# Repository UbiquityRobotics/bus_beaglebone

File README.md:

# bus_beagle_bone

A Beagle Bone Black that can be connected to a bus.

The bus is a half-duplex multi-drop bus that runs at 500 Kbps.
It uses a Microchip MCP2562 CAN bus transceivers to connect to
the bus.

## Revision A

The schematic can be found in the `rev_a` folder as
`bus_raspberry_pi.pdf`.

### Power Supply

The power comes in on either N1 or N2.  These two connectors
are "daisy-chained" so that power can be routed to other boards.
The power goes through Q1 -- a P-channel MOSFET with a very low
R<Sub>ds</Sub>.  Q1 is used to prevent reverse polarity damage
just in case the power comes in reversed.  The power continues
to N6 which is a 5V DC-to-DC power converter that provides up
to 1.5 Amperes of output.  The 5V converter takes a nominal 24V
input with an absolute maximum of 36V.

### Bus Connection

The bus connection is on N3, which is a 2x5 .1 inch pitch
shrouded header.  LGND1 and LGND2 are connected to ground.
CANH and CANL are routed over to U2 which is the CAN bus
(more correctly -- a ISO-11898) transceiver -- a Microchip
MCP2562.  The TXD and RXD outputs are routed to the RXD1 and
TXD1 pins on the ATmega324P processor (U3).

### ISP Connection

The ISP connector is the 2x3 .1 inch pitch connector (N7)
that is connected to the MOSI, MISO, #RESET, and SCK pins
on the processor (U3).

### JTAG Connection

The JTAG connector is N9 which is also a .1 inch 2x5 shrouded
header.  The TDI, TDO, DMS, TCK, and #RESET lines are connected
to the appropriate JTAG pins on the processor (U3).

### 3.3 vs 5V Volt Issues

The processor (U3), AND gates (U1), and CAN bus transceiver (U2)
all run at 5V.  The USB to serial connectors (N4, N5) and the
Raspberry Pi connector (N10) use 3.3V signal levels.  Thus,
there are numerous places where 3.3V vs. 5V signal levels have
to be dealt with.

The signal level conversion is done with a 74HCT08 quad 2-input
AND gate (U1).  The HCT logic family is capable of converting TTL
voltage levels into "high" and "low" signals.  In particular,
the HCT logic family treats any voltage above 2.0V as a logic
"high."

There are 7 separate 22K/33K voltage dividers used for voltage
level issues.  The seven 22K resistors are contained in an 8-pin
SIP (Serial In-line Package.)  These seven resistors are named
R1A through R1F.  Likewise, the seven 33K resistors are contained
in another 8-pin SIP and are named R2A through R2F.  The voltage
dividers are deliberately arranged so that they have the letter
suffix -- R1A/R2A, ... , R1F/R2F.

The nominal center tap voltage of a 22K/33K voltage divider is:

    Vin * 33K/(22K+33K) = Vin * 3/5.

With Vin equal to 5 volts, the center tap voltage is 5V * 3/5 = 3V.

These 8-pin serial in-line packages have a resistance tolerance
of 2%.  This results in a center tap voltage range from 2.88V
to 3.12V.  2.88V is greater than the 2.0 Vih<Sub>min</Sub> for
the HCT logic family.  2.88V is also greater than .7*Vcc
(=.7*3.3V=2.31V) which is the standard Vin<Sub>min</Sub> for
standard CMOS.  3.12V is less than VCC (=3.3V).  Hence, the
voltage divider does not produce illegal 3.3V signaling levels.

Whenever a 5V output needs to be converted from 5 volts to 3V,
it directly fed into a voltage divider.  This occurs with R1D/R2D
connected to TXD0 of the processor (U4) and R1E/R2E and the
output of U1C.

The remaining five voltage dividers are all inputs of the 
74HCT08 quad AND gate package.  There are three cases to
be considered:

* When there is no connection, the voltage divider will 
  pull the input pin to a nominal 3V which is treated as
  a logic high.

* a 3.3V signal is connected, it will be at either 0V or 3.3V.
  In either case, the provided 3.3V voltage signal "overrides"
  the voltage divider.

* For the USB to serial connectors (N4, N5), it is possible
  to accidentally connect in a 5V USB to serial cable.  Again,
  in this case, the provided 5V voltage signal "overrides"
  the voltage divider.  The 74HCT05 is perfectly happy to
  tolerate a 5V input signal.

### Reset Circuitry

The reset signal can be sourced from four locations:

* The manual reset push button -- SW1,

* The #NRST on the JTAG connector (N9),

* The GPIO110_SPI1_SCLK pin on N10, and

* The #RTS signal (3.3V) on the programming FTDI connector (N4),

The push button is the simplest.  It connects the #RESET line
to ground when pushed.  Done.

Similarly, the #NRST line on the JTAG connector (N9) can be
driven low by a JTAG programmer/debugger.  Done.

Both the #RTS signal from N4 and the GPIO110_SPI1_SCLK pin
from N10 are used to trigger temporary reset pulse.  The basic
circuit is C6, D1 and R4 for #RTS/N4 and C8, D1 and R4.
Since the circuit is basically the same for both branches,
only the #RTS/N4 branch is explained.

The reset circuit from #RTS/N4 adheres to the Arduino defacto
standard for reset.  The signal comes in on pin 2 of U1A.
A voltage divider R1B/R2B holds the line at a nominal 3V
if no serial cable is plugged in.  Pin 1 of U1A is tied
to 5V so that U1A operates as a simple 3.3V to 5V voltage
level converter.

When the Arduino programmer (usually AVRDUDE) opens the connection
to the serial cable, #RTS (Request to Send) is driven low
for the duration of the programming session.  Capacitor C6, D1,
and R4 are used to convert the falling edge of #RTS into a
pulse onto the #RESET line.

* Prior to asserting #RTS low, the U1A 5V output and the
  R4 10K pull-up resistor hold both ends of capacitor C6
  at 5V.  This completely discharges C6.

* When #RTS goes low at the start of programming, the U1A
  output also goes low.  Since there is no voltage across
  C6, the other end of C6 is driven low as well.  This
  causes the #RESET line to be asserted low.

* Now C6 starts getting charged via R4 and starts to develop
  5V across C6.  Eventually the voltage across C6 will get
  high enough to de-assert #RESET and the processor (U3)
  will start to run the boot-loader.o

* When the programming session is over, #RTS is driven high.
  The causes the output of C6 to attempt to jump from 5V
  up to 10V.

<Pre>
        10V |                           *
            |                           **
            |                           * ***
            |                           *    ****
            |                           *        *****
        5V  ********              *******             *******
            |      *        ******      ^
            |      *    ****            |
            |      * ***                |
            |      **                   |
        0V  +------*--------------------|----------------------->
                                        |
                   ^                    |
                   |                    |
               #RTS goes low       #RTS goes high
</Pre>

* To prevent the voltage from going up to 10V, the Schottky
  diode D1 clamps the voltage to no more than 5.2V by very
  rapidly discharging C6.

The reason why a Schottky diode is used instead of a silicon
diode is because it unclear what the voltage tolerance of #NRST
of the JTAG programmer connector (N9) and the #RESET connector
of the ISP connector (N7) are.  By using a Schottky diode,
the voltage is clamped to 5.2V rather than 5.7.

### RXD and TXD Considerations

In general, the primary purpose of this board is to connect
TXD0 and RXD1 to GPIO2_UART2_RX and GPIO3_UART2_TX respectively.
In addition, it is desirable to allow the programming
connector (N5) to be used to program the processor (U4)
*and* to use the console connector (N5) to view the console
traffic from the Raspberry Pi on boot up.  To accomplish this
task some additional circuitry is used to OR the serial
cable TXD signals into the correct locations.

A key thing to understand about serial connections is that
the line idles "high".  U1B and U1D are AND gates.  Using
De Morgan's law, A.B = ~(~A + ~B).  Thus, using 2-input AND
gates, the signals a correctly OR'ed together so that when
both inputs are idling "high", the output is also "high".

There are three paths to follow:

* Processor (U4) <==> Raspberry Pi (N9),

* Processor (U4) <==> programmer connector (N2), and

* Processor (U4) <==> console connector (N3).

#### Processor to Raspberry Pi

In this situation, the 5V TXD0 output on the processor (U3)
is routed through the R1D/2D voltage divider to bring the
voltage down to a nominal 3.0V.  This signal is routed to U1C.
U1C converts the 3.0V signal to a 5V output which is again
divided back down to 3.0V via R1E/R2E.  This 3.0V signal goes
into GPIO2_UART2_RX on the Raspberry Pi.

In the reverse direction, the 3.3V output of GPIO15_TXD is
sent through the R1G/R2G voltage divider U1B which converts
it to a 5V output and directs it to RXD0 on the processor (U3).

#### Processor to Programmer Connector

In this situation, the 5V TXD0 output on the processor (U3)
is voltage divided by R1D/R2D down to 3.0V and goes to RXD
on the programmer connector (N2).

The 3.3V TXD output on the programmer connector (N2) is
routed to U1B which converts it up to 5V and routes the
signal into RXD0 input on the processor (U4).

#### Processor to Console Connector

In this situation, the 5V TXD0 output on processor (U4)
is voltage divided R1D/R2D down to 3.0V and to both U1C
and the RXD signal of N4.

The GPIO3_UART2_TX is routed through the R1G/R2G voltage
divider directly to the RXD pin of N5.

## LED Circuit

The LED circuit is provides a single LED (D2) that can be

* connected to the power supply to provide a power on LED, or

* connected to PB7/SCK (aka the Arduino D13 pin) of the
   processor (U3), or

* can be left unconnected.

This is accomplished using J1, R5, R6 and D2.

When pins 1 and 3 of J2 are shorted using a jumper, power is
routed from +5V through R6 through the LED (D2) to ground.

When pins 2 and 3 of J2 are shorted together, the output
of PB7/SCK of the processor (U3) is routed through R5 
through the LED to ground.

When pins 3 and 4 of J2 are shorted together, there is
no circuit path through LED (D2).

When pins 1 and 2 of J2 are accidentally shorted together,
resistors R5 and R6 form a voltage divider that simply
wastes power.  At least it does not accidentally short
the power supply to ground.

## Rev. A Issues

* JTAG NRST is not connected to #RESET. [x]

* R1D is connected to +5V not TXD0. [x]

* R1E is connected to +5V not U1C output. [x]

* R1G is connected to +5V not GPIO2_UART2_RX. [x]

* C6 and C8 should be 1uF. [x]

* The MCP2562 (U2) RxD and Txd (pins 1 and 4) are swapped. [x]

* Add 100K pull up resistor inputs that can be disconnected. [x]

* Make sure the BBB connector edge is clear of obsticles.
  Think about making N10 (the BBB connector) the full length. [x]

* Think about connecting MCP2562 (U2) STBY (pin 8) to a processor pin.

* Rotate N3 (the bus connector); it is pointing the wrong way. [x]

* C1 can be moved to be in line with C2. [x]

* N4 is labeled "CONSOLE" and N5 is labeled "PROGRAM".  This is backwards. [x]

* The artwork for N6 (the power supply connector) is backwards. [x]

## Rev. B Issues

* Move N10 closer to the PCB edge. [x]

* Think about add two pins next to N10 to prevent miss aligning
  N10 along the P9 row.  [Added N11, N12, and N13]

* Added real time clock. [x]

## Rev. C Issues

* Pin 10 of U1 has no 100K pull-up. [done]

* ISP connector is too close to real time clock to work with the
  Atmel-ICE programmer.  There is actually plenty of room around
  the crystal and load capacitors. [done]

* The hole for the plus terminal of the Litium battery is way
  too big.

* The 5mm Terminal blocks are oriented backwards. [removed]

* Think about changing the 1x1 mis-alignment pins for the
  BBB connector to 1x2's.  They would be easier to install. [done]

* Think about removing the R9/R10 pull-up resistors.  The BBB
  already has pull-up resistors. [done]

* The Lithium battery overlaps with the JTAG connector.  Perhaps
  rearrange. [done]

* There is no filter capacitor for the real time clock.

* The RC constant of R4 * (C6 + C8) needs to be small enough
  that the circuit will actually reset before jumping to location 0.
  When both C6 and C8 are 1uF, the RC constant is too big.
  Thus, probably C6 and C8 should be set to .1uF. [done]

* N7 is too close to N6.  It is really hard to jumper the LED
  to be connected to D13. [5V Regulator changed]

* N6 is artwork is not next to actual N6 connector. [done]

* N6 would have mechanical interferance with N2. [done]

* Think about adding lines to the BBB POWER button and reset.
  [not done]

* The Ground on pins 1 and 2 of the BBB connector is not very good.
  [done]

* Pin 31 is hooked to a high frequency SPI signal.  It should be
  connected to a slower GPIO line. [done]

* Think about adding a female USB A connector to provide 5V to
  other devices that need 5V. [see bus_usb_power]

## ROS Integration

It is desirable to have excellent ROS integration with "the bus".
The bus has the following features:

* Discovery.  The head processor can scan the bus and find all
  modules that are plugged into it.  Currently, hot plugging
  is not allowed, but it could if future versions.

* Flexibility.  While bus modules can be dedicated to a single
  task, some of them are more fleximble.  For example,

  * bus_grove12 can be connected to 100+ different Grove system modules.

  * bus_micro?? can be connected to 100+ diffeent MikroBus modules.

  * bus_dynabus can be connected to dozens of Dynamixel servos.

* Field Upgradable. The firmware for each module can be upgraded
  of the bus.

The bus is basically operated in a master/slave mode.  ROS talks
to a bus master (e.g. bus_beaglebone) via a serial protocol.
The bus master talks to the bus modules using bus protocol.

The ROS bus node is a ROS node that talks to the bus master
over a serial line.  Only the ROS bus node is allowed to use
the serial line connected to the bus master.  Any other ROS
nodes that need to access the bus must do so through the ROS
Bus node.

It is anticipated that each bus module will have a corresponding
ROS node that is responsible for the bus module.  

correspondance to bus modules and a ROS node to control the
bus module.  For example, the bus_sonar10 module will have
a didicated ROS Sonar10 node.  

### ROS Bus Node

The basic concept behind the ROS Bus Node is that allows other
ROS nodes to talk to the bus via a modes number of ROS service
(i.e. Remote Procedure Call) requests.

        login("node id TBD") => session
            Returns a session handle for subsequent requests.

        logout(session)
            Lets Bus Node that session is not to be accepted
            anymore.

        bus_search(session, vendor_id, product_id) => [bus_uid,...]
            Return list of bus_uid's for bus modules that match
            vendor_id and product_id.  vendor_id and product_id
            can be set to 0 to matach all.

        hardware_version(session, bus_uid) => hardware_version
            Return the hardware version for bus_uid.

        firmware_version(session, bus_uid) => (major, minor)
            Return the major and minor software version numbers
            for bus_uid.

        attach(session, bus_uid, share) => module
            Returns a module handle for talking to the bus_id.
            Set share to 1 for a sharable module and to 0 for
            exclusive use.

        release(session, module)
            Releases module.

        transfer(session, module, priority, [byte, ...]) => [byte, ...]
            This is the generic bus message send receive message.
            Mostly, people will use higher level commands.  Priority
            specifies the immediacy of the message.

        register_get(session, module, priority, register) => value
            Set register to value.  Value is is a scalar value
            that is up to 32-bits.

        register_set(session, module, priority, register, value, size)
            Set register to value.  Value is is a scalar value
            that is up to 32-bits in size.  size specifies the number
            bytes.

        string_get(session, module, priority, register) => "text"
            Get a string value from a string register.

## Bus_Bridge_Encoders_Sonar Node

Basically this node has to emulate the functionality of the
ROS Arduino Bridge.

* Publish odometry data

* Accept drive requests (i.e. speed and twist)

* Publish sonar data

## Serial Line Protocol

        Host => Coprocessor:

            1100 00hh        Set hh
            1100 0100        Do Discovery scan
            1100 0101        Reset bus
            1100 0110        Reserved
            1100 0111        Reserved

            xyyy yyyy        if (hh > 0) { send (h hyyy yyyy); hh = -1; }
                                     else      { send (0 xyyy yyyy); }

        Coprocessor => Host:
            a xxxx xxxx	     Send xxxx xxxx to host (9th bit is lost)

## Installing ROS Hydro Onto a Micro-SD Card

1. Create a ros-bbb directory:

        cd ...
        mkdir ros-bbb
        cd ros-bbb

2. Download the following three files from ros-training.com:

        wget http://www.ros-training.com/static/media/ros-bbb/ubuntu_ros_partitions.sfdisk
        wget http://www.ros-training.com/static/media/ros-bbb/ubuntu_ros_boot.partimg.gz.000
        wget http://www.ros-training.com/static/media/ros-bbb/ubuntu_ros_rootfs.partimg.gz.000

3. Verify that you got files that are the right size:

        ls -la
        -rw-rw-r-- 1 wayne wayne   6916451 Aug 22 08:01 ubuntu_ros_boot.partimg.gz.000
        -rw-rw-r-- 1 wayne wayne       259 Aug 22 08:01 ubuntu_ros_partitions.sfdisk
        -rw-rw-r-- 1 wayne wayne 345502689 Aug 22 08:09 ubuntu_ros_rootfs.partimg.gz.000

4. *Before* put your micro-SD card in, see what /dev/sd* says:

        ls -l /dev/sd*
        brw-rw---- 1 root disk 8,  0 Aug 22 10:33 /dev/sda
        brw-rw---- 1 root disk 8,  1 Aug 22 10:33 /dev/sda1
        brw-rw---- 1 root disk 8,  2 Aug 22 10:33 /dev/sda2
        brw-rw---- 1 root disk 8,  3 Aug 22 10:33 /dev/sda3
        brw-rw---- 1 root disk 8,  4 Aug 22 10:33 /dev/sda4
        brw-rw---- 1 root disk 8,  5 Aug 22 10:33 /dev/sda5
        brw-rw---- 1 root disk 8,  6 Aug 22 10:33 /dev/sda6
        brw-rw---- 1 root disk 8,  7 Aug 22 10:33 /dev/sda7

5. Now insert your 8GB (or larger) micro-SD card into the slot and
   do another ls command:

        ls -l /dev/sd*
        brw-rw---- 1 root disk 8,  0 Aug 22 10:33 /dev/sda
        brw-rw---- 1 root disk 8,  1 Aug 22 10:33 /dev/sda1
        brw-rw---- 1 root disk 8,  2 Aug 22 10:33 /dev/sda2
        brw-rw---- 1 root disk 8,  3 Aug 22 10:33 /dev/sda3
        brw-rw---- 1 root disk 8,  4 Aug 22 10:33 /dev/sda4
        brw-rw---- 1 root disk 8,  5 Aug 22 10:33 /dev/sda5
        brw-rw---- 1 root disk 8,  6 Aug 22 10:33 /dev/sda6
        brw-rw---- 1 root disk 8,  7 Aug 22 10:33 /dev/sda7
        brw-rw---- 1 root disk 8, 16 Aug 22 18:50 /dev/sdb
        brw-rw---- 1 root disk 8, 17 Aug 22 18:50 /dev/sdb1

   Notice that /dev/sdb and /dev/sdb1 showed up.  If something
   else shows up, you are going to need to manually edit
   ubuntu_ros_partitions.sfdisk file.  In addition, everywhere in
   the instructions below, you are going to have to change
   "/dev/sdb..." into /dev/sdX..." where "X" is the correct
   micro-SD drive letter.  If this does not make any sense,
   *get some help*.

6. I do the next commands as root:

        sudo bash
        Password: {your root password here}

7. Make sure that the partimage command is installed:

        apt-get install partimage
        {Respond positively to all prompts}

8. Make darn sure that /dev/sdb* is not installed:

        umount /dev/sdb*
        {It should say everything is unmounted}

9. Install a partition table on /dev/sdb:

        sfdisk --force /dev/sdb < ubuntu_ros_partitions.sfdisk
        partprobe /dev/sdb
        partprobe -s /dev/sdb

   The partprobe -s command may mention "msdos", just ignore that.

10. Now install boot image on micro-SD card:

        partimage restore /dev/sdb1 ubuntu_ros_boot.partimg.gz.000

    This will bring up one of the fake ASCII window system.
    You can use [Tab] to advance from one option to the next
    You can use [space] to toggle an option.
    You can type [enter] to trigger everything.
    For this screen I only toggle the option that writes 0's
    to empty blocks.  It is probably unnecessary, but I like
    to be sure.  Type [enter] at the continue option.  Keep
    typing [Tab]'s and [returns] until it actually write the
    partition bits.  The program will finish and then pause
    for a while as it finishes flushing the bits out to the
    micro-SD card.  Just be patient.

11. Now install rootfs partition onto the micro-SD card:

        partimage restore /dev/sdb2 ubuntu_ros_rootfs.partimg.gz.000
                
    Go through the same steps as in step 10.

12. Make darn sure that /dev/sdb* is unmounted:

        umount /dev/sdb*
        {It should say everything is no longer mounted}

14. Make sure that minicom is installed:

        apt-get install minicom

14. Exit from root:

        exit

15. Yank the micro-SD card out of your machine.

16. Grab your Beaglebone Black (henecforth called BBB.)  Flip it
    over and install the micro-SD card.

17. Find two open USB ports on your laptop/desktop.  Plug your
    FTDI 3.3V USB to serial cable into one of the USB ports.
    Make *darn* sure that you have a 3.3V FTDI cable.  If you
    are using one of Wayne's FTDI cables with tape wrapped
    arround the pin, peel the tape back and make *sure* it
    says "3V3" on the USB connector.  Plug the short USB to
    mini-USB cable that came with your BBB into the other USB
    port on laptop/desktop.  Do *not* plug the other end of
    this cable into the BBB yet.

18. On the top of the BBB, there is a 1x6 pin header labeled J1.
    One of the pins has a white dot next to the pin.  Plug in
    the 1x6 female receptical on the FTDI cable such that the
    black wire goes into the next the white dot.

19. Fire up the minicom terminal emulator:

        minicom

    Make sure the baud rate is "115200 8N1".  It should specify
    that it is using a serail cable like /dev/ttyUSB0.

20. Locate the little black button on the top surface of the BBB
    on that is near the micro-SD card (which is on the back surface).
    This button is very close to one of the mounting holes.  Also
    locate the micro-USB connector on the back side of the BBB
    near the Ethernet Jack (which is on the front side.)

21. Now we will carefully power up the BBB.  This is done by:

    A. Press down the black button and *hold* it down.
    B. While leaving the black button held down, plug in
       the power micro-SD.
    C. The blue LED's flash on the BBB.
    D. Boot up text spews out on the minicom window.

22. In fairly short order, Linux 13.04 will boot up and prompt
    you to login.  You can login as either user "ubuntu" with
    password "temppwd" or as user "ros" with password "training".

23. After you have logged in, you can poke around.  Verity that
    the directory "/opt/ros/hydro" exists.

24. Now you can shut down the BBB:

        sudo halt
        Password: {Use "temppwd" or "training")

    Some lights flash and some text spews.  Eventually the BBB
    stops.

25. Remove power cable and USB-to Serial cable.

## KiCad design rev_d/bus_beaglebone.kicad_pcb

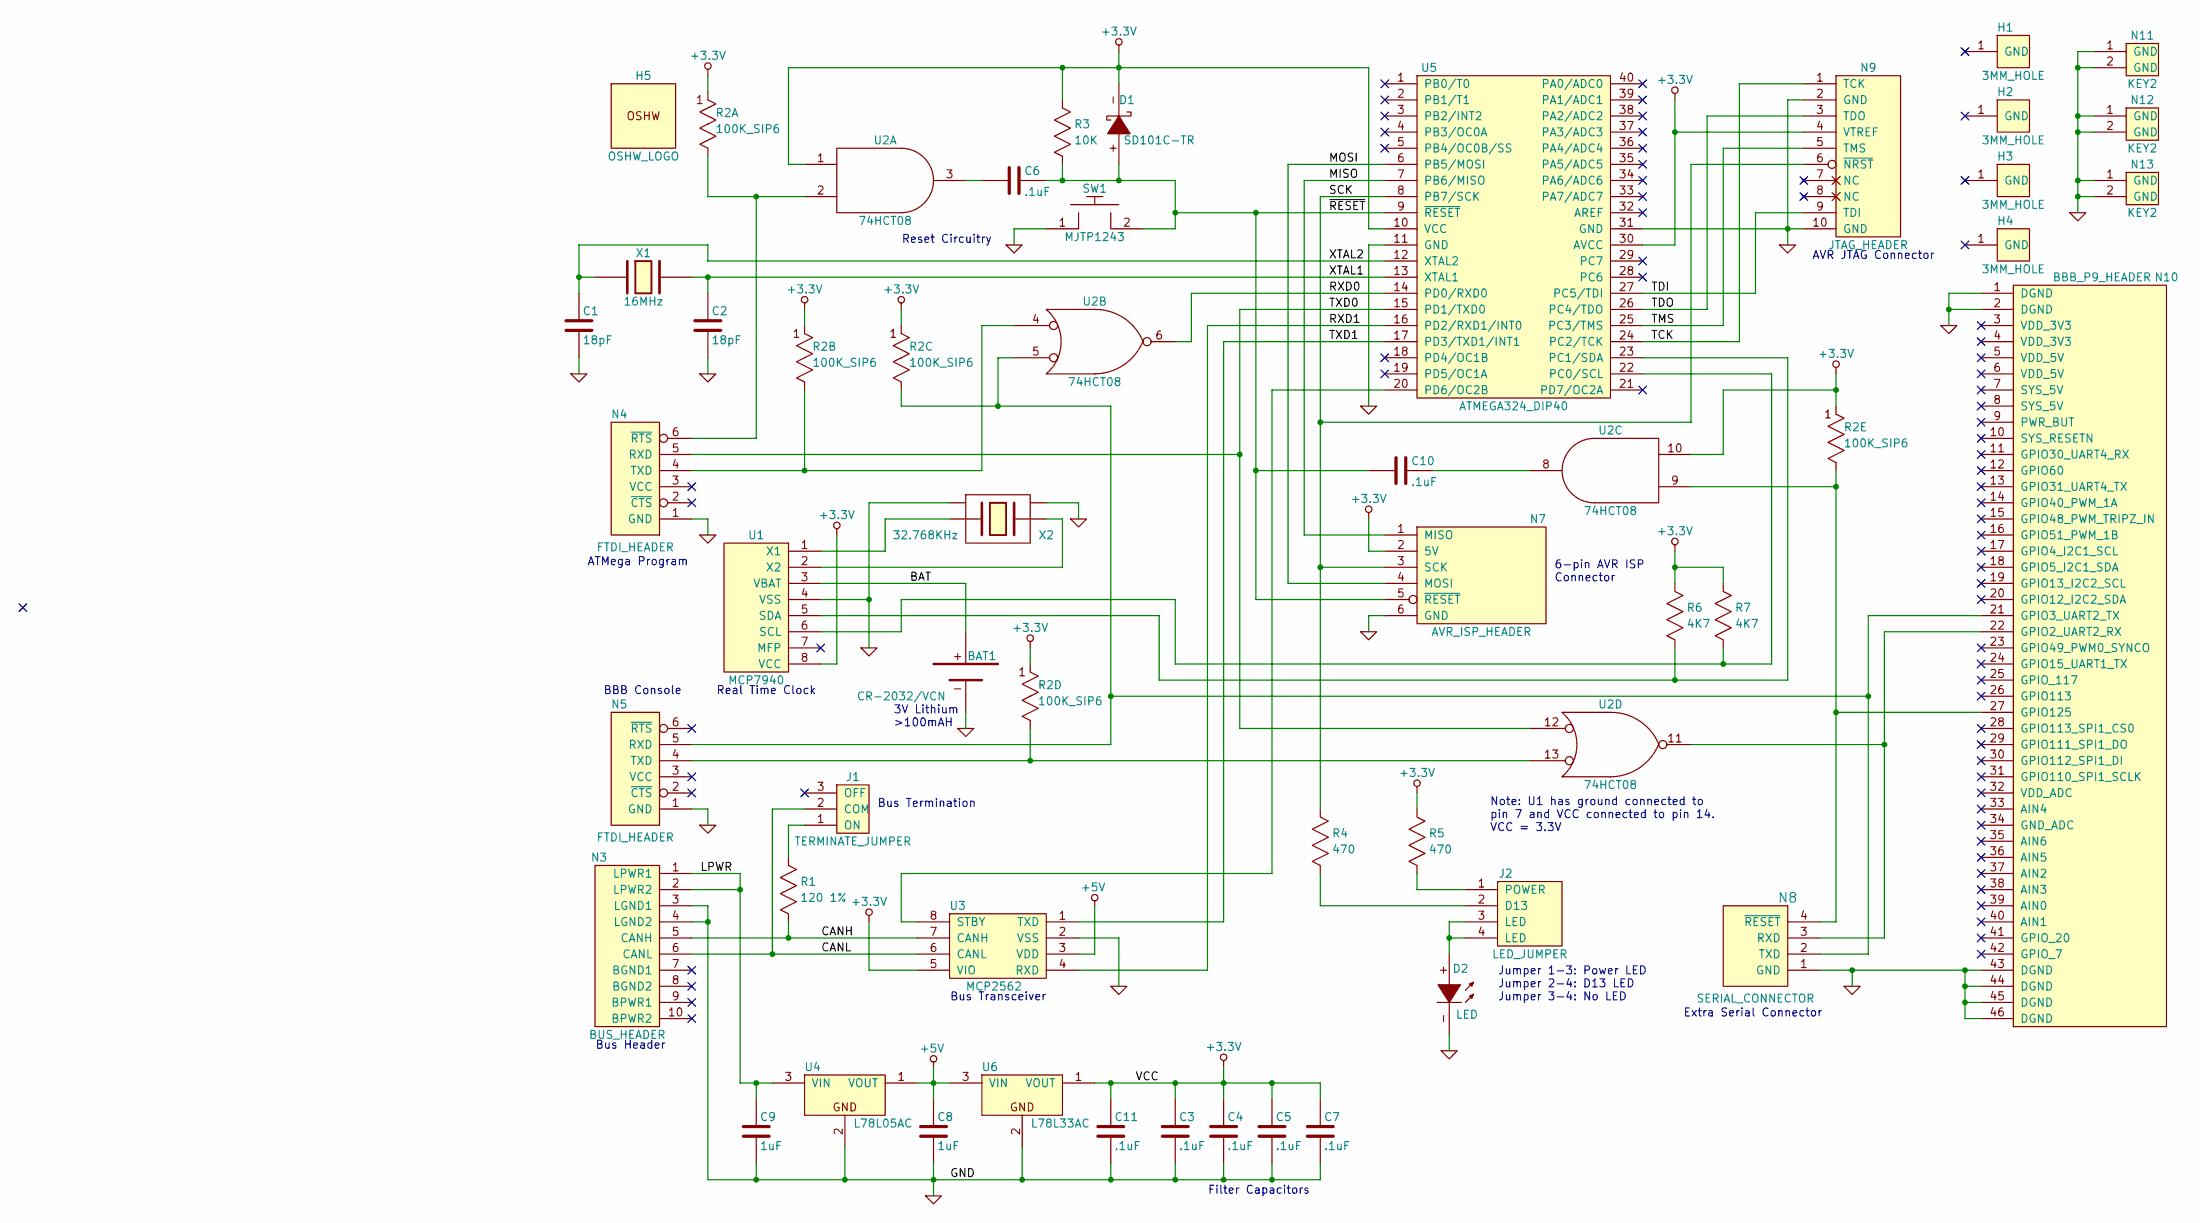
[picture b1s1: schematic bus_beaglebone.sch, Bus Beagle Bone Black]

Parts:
BAT1: CR-2032/VCN; 10MM_BATTERY
C1, C2: 18pF; Capacitor3MMDiscRM2.5
C3, C4, C5, C6, C7, C10, C11: .1uF; Capacitor3MMDiscRM2.5
C8, C9: 1uF; Capacitor3MMDiscRM2.5
D1: SD101C-TR; Diode_DO-41_SOD81_Horizontal_RM10
D2: LED; T1_LED
H1, H2, H3, H4: 3MM_HOLE; MountingHole_3mm
H5: OSHW_LOGO; OSHW_LOGO_250mil
J1: TERMINATE_JUMPER; Pin_Header_Straight_1x03
J2: LED_JUMPER; Pin_Header_Straight_2x02
N3: BUS_HEADER; Pin_Header_Straight_2x05_Shrouded
N4, N5: FTDI_HEADER; Pin_Header_Straight_1x06
N7: AVR_ISP_HEADER; Pin_Header_Straight_2x03
N8: SERIAL_CONNECTOR; Pin_Header_Straight_1x04
N9: JTAG_HEADER; Pin_Header_Straight_2x05_Shrouded
N10: BBB_P9_HEADER; Pin_Header_Straight_2x23
N11, N12, N13: KEY2; Pin_Header_Straight_1x02
R1: 120 1%; Resistor_Horizontal__400
R2: 100K_SIP6; Pin_Header_Straight_1x06
R3: 10K; Resistor_Horizontal__400
R4, R5: 470; Resistor_Horizontal__400
R6, R7: 4K7; Resistor_Horizontal__400
SW1: MJTP1243; Button_6.5MM
U1: MCP7940; DIP-8__300
U2: 74HCT08; DIP-14__300
U3: MCP2562; DIP-8__300
U4: L78L05AC; TO92_123
U5: ATMEGA324_DIP40; DIP-40__600
U6: L78L33AC; TO92_123
X1: 16MHz; Crystal_HC49-U_Vertical
X2: 32.768KHz; RTC_CRYSTAL

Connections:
+3.3V: C3.1, C4.1, C5.1, C7.1, C11.1, D1.-, N7.2 (5V), N9.4 (VTREF), R2.1, R3.2, R5.2, R6.2, R7.2, U1.8 (VCC), U2.1, U2.10, U2.14 (VCC), U3.5 (VIO), U5.10 (VCC), U5.30 (AVCC), U6.1 (VOUT)
+5V: C8.1, U3.3 (VDD), U4.1 (VOUT), U6.3 (VIN)
/BAT: BAT1.+, U1.3 (VBAT)
/CANH: N3.5 (CANH), R1.1, U3.7 (CANH)
/CANL: J1.2 (COM), N3.6 (CANL), U3.6 (CANL)
/LPWR: C9.1, N3.1 (LPWR1), N3.2 (LPWR2), U4.3 (VIN)
/MISO: N7.1 (MISO), U5.7 (PB6/MISO)
/MOSI: N7.4 (MOSI), U5.6 (PB5/MOSI)
/RXD0: U2.6, U5.14 (PD0/RXD0)
/RXD1: U3.4 (RXD), U5.16 (PD2/RXD1/INT0)
/SCK: N7.3 (SCK), N9.6 (~NRST), R4.2, U5.8 (PB7/SCK)
/TCK: N9.1 (TCK), U5.24 (PC2/TCK)
/TDI: N9.9 (TDI), U5.27 (PC5/TDI)
/TDO: N9.3 (TDO), U5.26 (PC4/TDO)
/TMS: N9.5 (TMS), U5.25 (PC3/TMS)
/TXD0: N4.5 (RXD), U2.12, U5.15 (PD1/TXD0)
/TXD1: U3.1 (TXD), U5.17 (PD3/TXD1/INT1)
/XTAL1: C2.1, U5.13 (XTAL1), X1.2
/XTAL2: C1.1, U5.12 (XTAL2), X1.1
/~RESET: C6.2, C10.1, D1.+, N7.5 (~RESET), R3.1, SW1.2, U5.9 (~RESET)
GND: BAT1.-, C1.2, C2.2, C3.2, C4.2, C5.2, C7.2, C8.2, C9.2, C11.2, D2.-, N3.3 (LGND1), N3.4 (LGND2), N4.1 (GND), N5.1 (GND), N7.6 (GND), N8.1 (GND), N9.2 (GND), N9.10 (GND), N10.1 (DGND), N10.2 (DGND), N10.43 (DGND), N10.44 (DGND), N10.45 (DGND), N10.46 (DGND), N11.1, N11.2, N12.1, N12.2, N13.1, N13.2, SW1.1, U1.4 (VSS), U2.7 (GND), U3.2 (VSS), U4.2, U5.11 (GND), U5.31 (GND), U6.2, X2.3 (GND), X2.4 (GND)
unnamed: C6.1, U2.3
unnamed: C10.2, U2.8
unnamed: D2.+, J2.3 (LED), J2.4 (LED)
unnamed: J1.1 (ON), R1.2
unnamed: J2.1 (POWER), R5.1
unnamed: J2.2 (D13), R4.1
unnamed: N4.4 (TXD), R2.3, U2.4
unnamed: N4.6 (~RTS), R2.2, U2.2
unnamed: N5.4 (TXD), R2.5, U2.13
unnamed: N5.5 (RXD), N8.2 (TXD), N10.21 (GPIO3_UART2_TX), R2.4, U2.5
unnamed: N8.3 (RXD), N10.22 (GPIO2_UART2_RX), U2.11
unnamed: N8.4 (~RESET), N10.27 (GPIO125), R2.6, U2.9
unnamed: R6.1, U1.5 (SDA), U5.23 (PC1/SDA)
unnamed: R7.1, U1.6 (SCL), U5.22 (PC0/SCL)
unnamed: U1.1 (X1), X2.1
unnamed: U1.2 (X2), X2.2
unnamed: U3.8 (STBY), U5.20 (PD6/OC2B)

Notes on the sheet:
BBB Console
ATMega Program
Note: U1 has ground connected to pin 7 and VCC connected to pin 14. VCC = 3.3V
Bus Header
6-pin AVR ISP Connector
Jumper 1-3: Power LED Jumper 2-4: D13 LED Jumper 3-4: No LED
Filter Capacitors
Bus Transceiver
Reset Circuitry
AVR JTAG Connector
3V Lithium >100mAH
Real Time Clock
Bus Termination
Extra Serial Connector

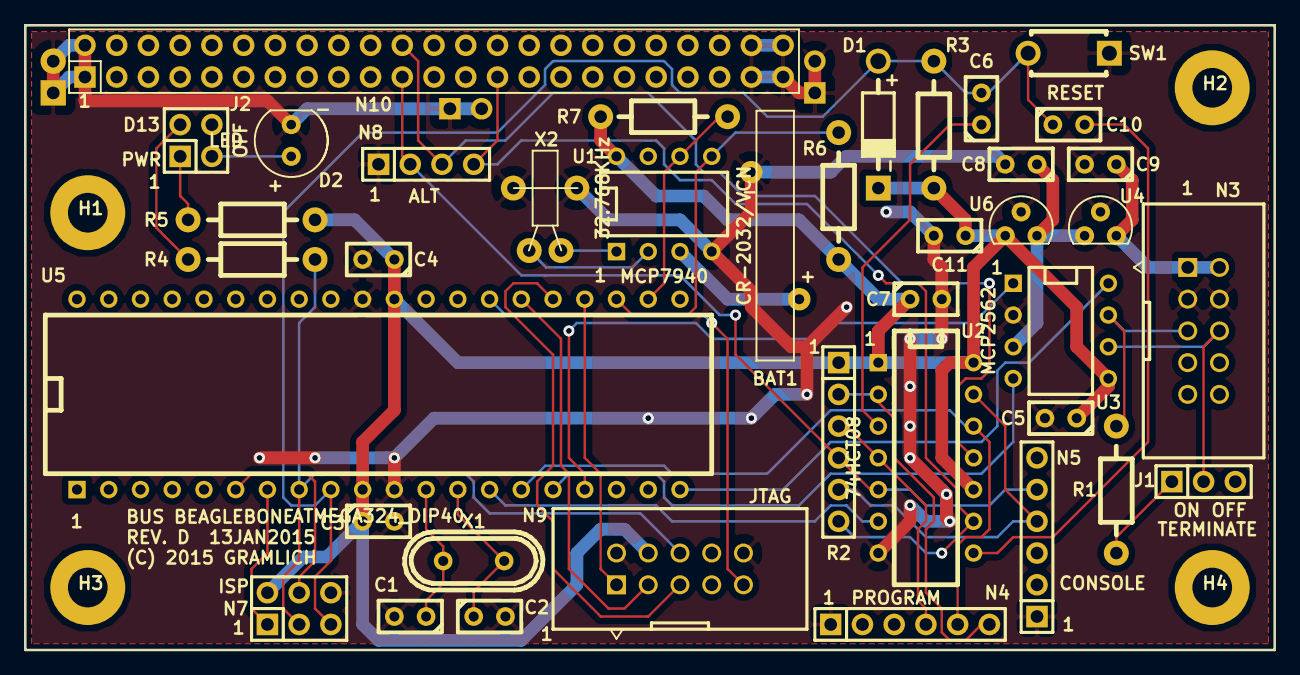
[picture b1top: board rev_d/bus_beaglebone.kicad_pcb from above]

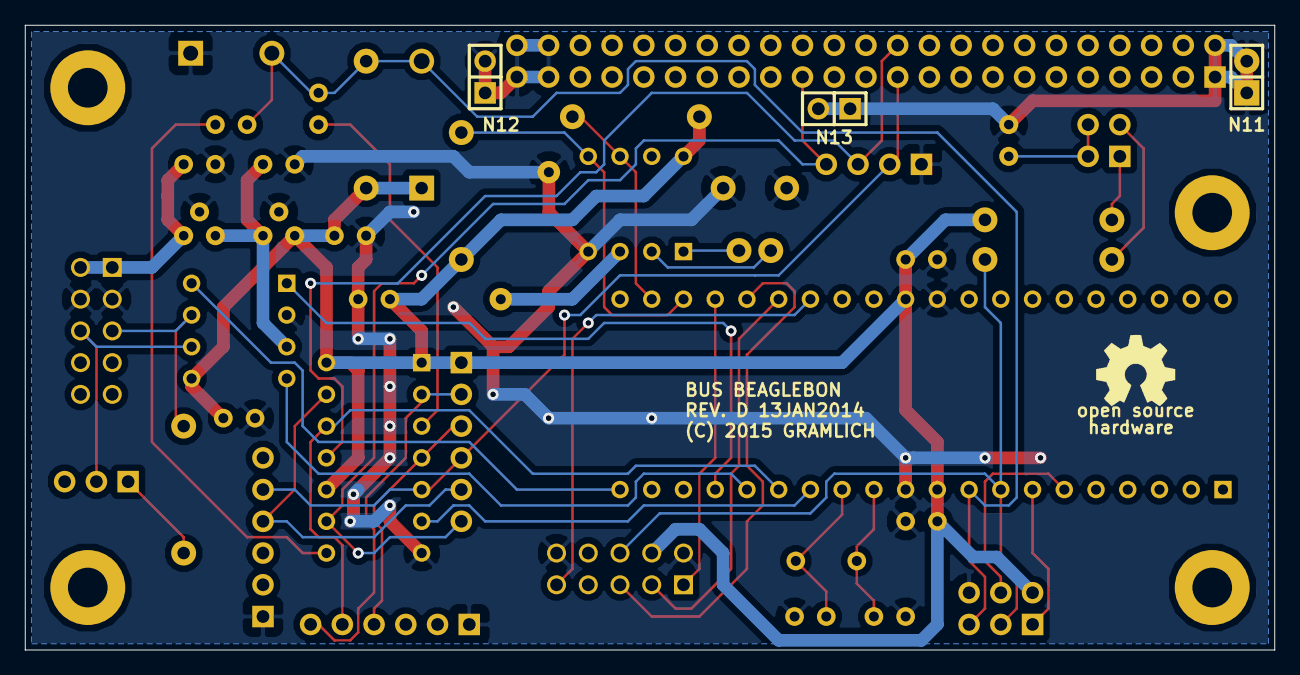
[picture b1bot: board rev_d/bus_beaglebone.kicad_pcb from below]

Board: 2 copper layers, 100.0 x 50.0 mm, 47 parts (4 on the bottom side), 38 nets.

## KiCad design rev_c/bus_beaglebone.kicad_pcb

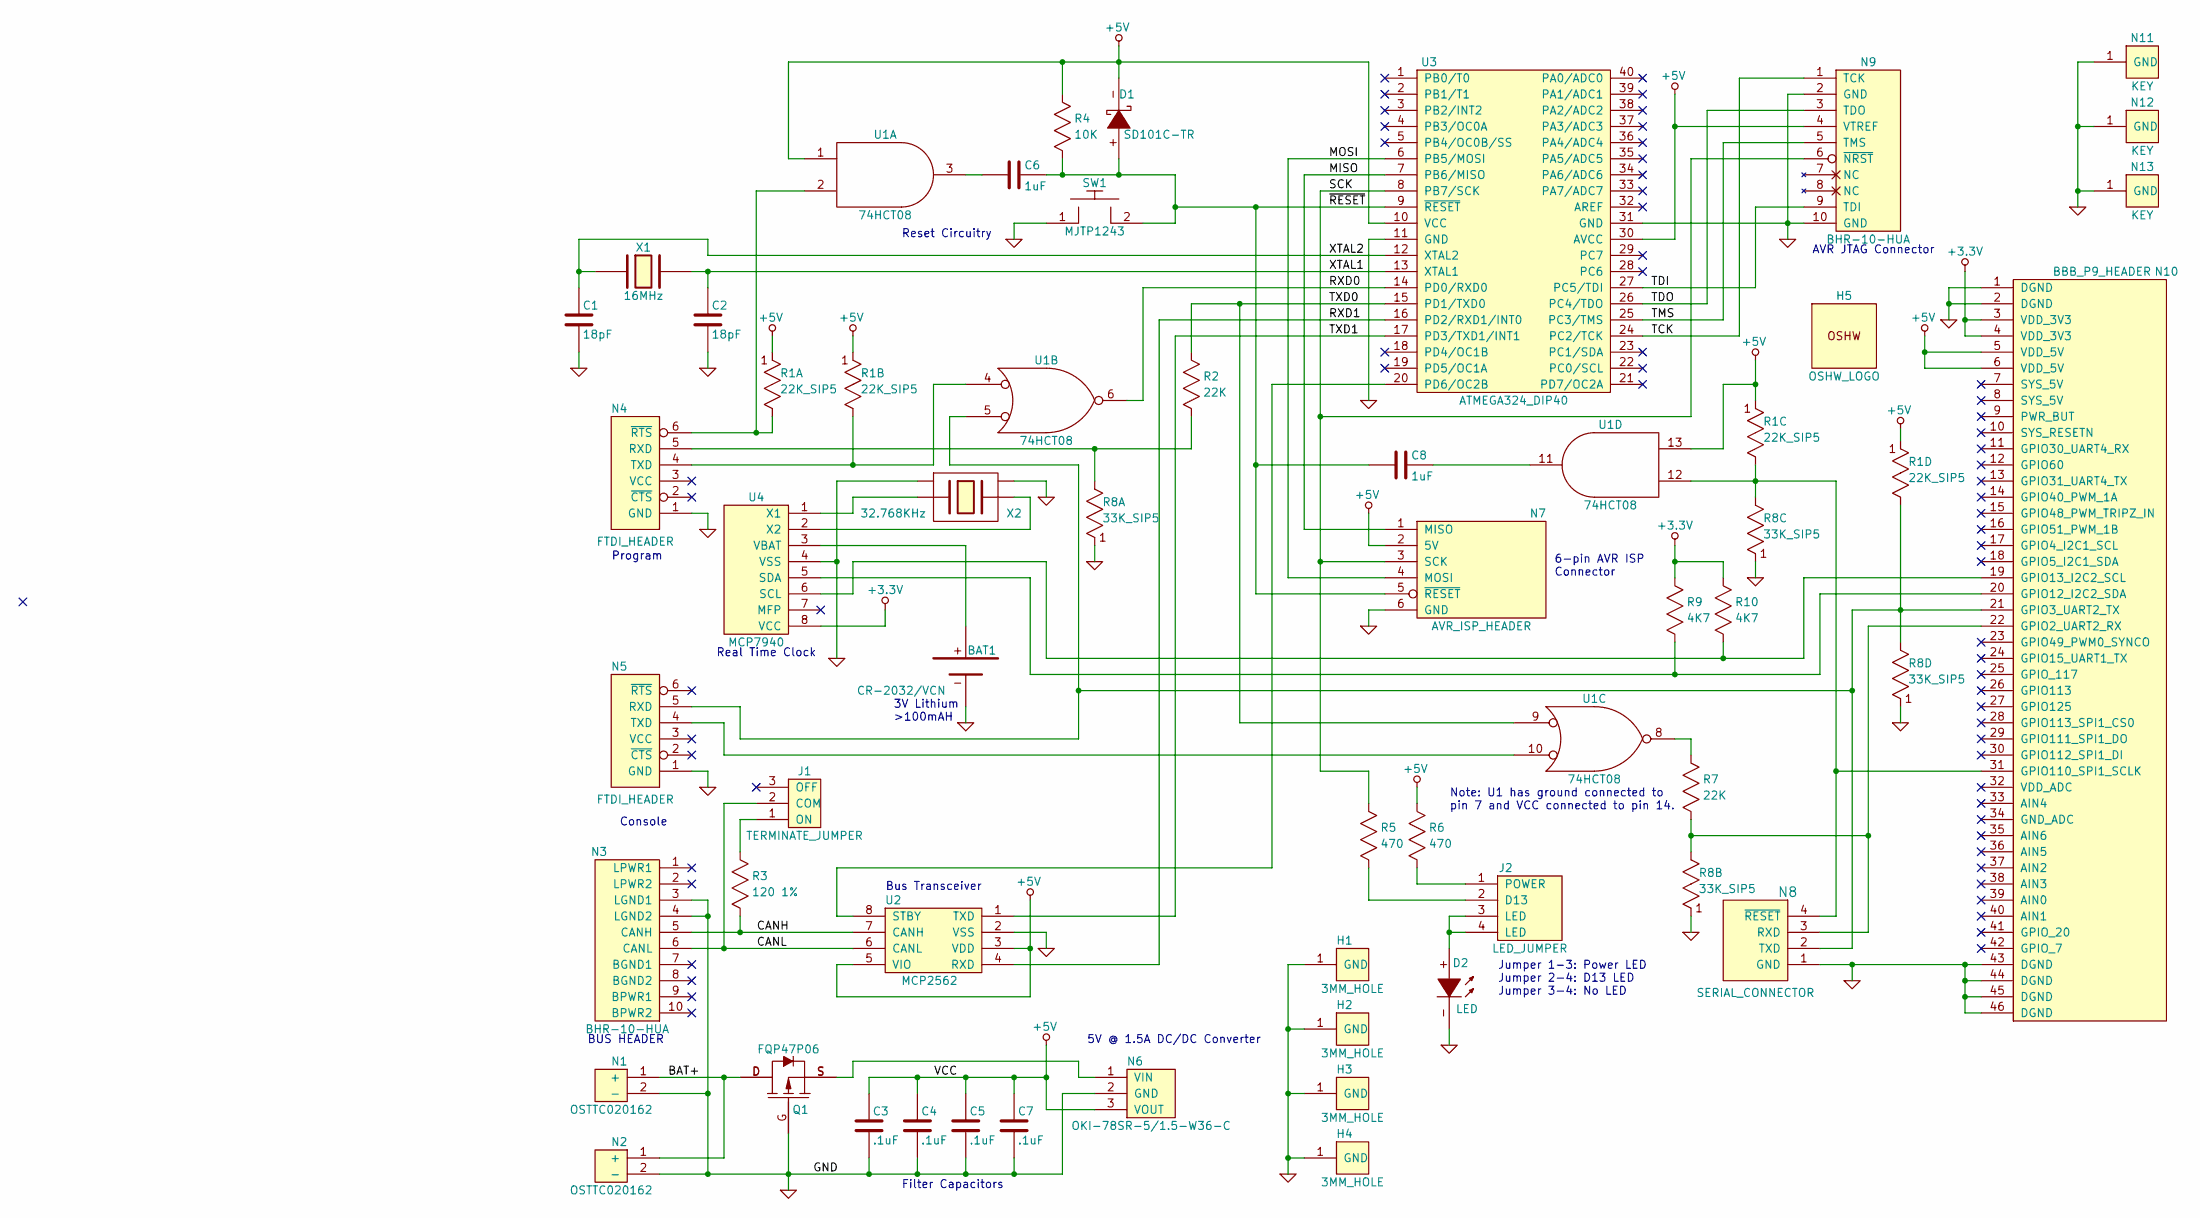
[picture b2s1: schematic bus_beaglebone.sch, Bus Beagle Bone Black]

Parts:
BAT1: CR-2032/VCN; 10MM_BATTERY
C1, C2: 18pF; Capacitor3MMDiscRM2.5
C3, C4, C5, C7: .1uF; Capacitor3MMDiscRM2.5
C6, C8: 1uF; Capacitor3MMDiscRM2.5
D1: SD101C-TR; Diode_DO-41_SOD81_Horizontal_RM10
D2: LED; T1_LED
H1, H2, H3, H4: 3MM_HOLE; MountingHole_3mm
H5: OSHW_LOGO; OSHW_LOGO_250mil
J1: TERMINATE_JUMPER; Pin_Header_Straight_1x03
J2: LED_JUMPER; Pin_Header_Straight_2x02
N1, N2: OSTTC020162; 5MM_TERMINAL_BLOCK_2_POS
N3, N9: BHR-10-HUA; Pin_Header_Straight_2x05_Shrouded
N4, N5: FTDI_HEADER; Pin_Header_Straight_1x06
N6: OKI-78SR-5/1.5-W36-C; OKI_DC_TO_DC_CONNECTOR
N7: AVR_ISP_HEADER; Pin_Header_Straight_2x03
N8: SERIAL_CONNECTOR; Pin_Header_Straight_1x04
N10: BBB_P9_HEADER; Pin_Header_Straight_2x23
N11, N12, N13: KEY; Pin_Header_Straight_1x01
Q1: FQP47P06; TO-220_FET-GDS_Horizontal_LargePads
R1: 22K_SIP5; Pin_Header_Straight_1x05
R2, R7: 22K; Resistor_Horizontal__400
R3: 120 1%; Resistor_Horizontal__400
R4: 10K; Resistor_Horizontal__400
R5, R6: 470; Resistor_Horizontal__400
R8: 33K_SIP5; Pin_Header_Straight_1x05
R9, R10: 4K7; Resistor_Horizontal__400
SW1: MJTP1243; Button_6.5MM
U1: 74HCT08; DIP-14__300
U2: MCP2562; DIP-8__300
U3: ATMEGA324_DIP40; DIP-40__600
U4: MCP7940; DIP-8__300
X1: 16MHz; Crystal_HC49-U_Vertical
X2: 32.768KHz; RTC_CRYSTAL

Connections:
+3.3V: N10.3 (VDD_3V3), N10.4 (VDD_3V3), R9.2, R10.2, U4.8 (VCC)
/BAT+: N1.1 (+), N2.1 (+), Q1.D
/CANH: N3.5 (CANH), R3.1, U2.7 (CANH)
/CANL: J1.2 (COM), N3.6 (CANL), U2.6 (CANL)
/MISO: N7.1 (MISO), U3.7 (PB6/MISO)
/MOSI: N7.4 (MOSI), U3.6 (PB5/MOSI)
/RXD0: U1.6, U3.14 (PD0/RXD0)
/RXD1: U2.4 (RXD), U3.16 (PD2/RXD1/INT0)
/SCK: N7.3 (SCK), N9.6 (~NRST), R5.2, U3.8 (PB7/SCK)
/TCK: N9.1 (TCK), U3.24 (PC2/TCK)
/TDI: N9.9 (TDI), U3.27 (PC5/TDI)
/TDO: N9.3 (TDO), U3.26 (PC4/TDO)
/TMS: N9.5 (TMS), U3.25 (PC3/TMS)
/TXD0: R2.2, U1.9, U3.15 (PD1/TXD0)
/TXD1: U2.1 (TXD), U3.17 (PD3/TXD1/INT1)
/XTAL1: C2.1, U3.13 (XTAL1), X1.2
/XTAL2: C1.1, U3.12 (XTAL2), X1.1
/~RESET: C6.2, C8.1, D1.+, N7.5 (~RESET), R4.1, SW1.2, U3.9 (~RESET)
GND: BAT1.-, C1.2, C2.2, C3.2, C4.2, C5.2, C7.2, D2.-, H1.1, H2.1, H3.1, H4.1, N1.2 (-), N2.2 (-), N3.3 (LGND1), N3.4 (LGND2), N4.1 (GND), N5.1 (GND), N6.2 (GND), N7.6 (GND), N8.1 (GND), N9.2 (GND), N9.10 (GND), N10.1 (DGND), N10.2 (DGND), N10.43 (DGND), N10.44 (DGND), N10.45 (DGND), N10.46 (DGND), N11.1, N12.1, N13.1, Q1.G, R8.1, SW1.1, U1.7 (GND), U2.2 (VSS), U3.11 (GND), U3.31 (GND), U4.4 (VSS), X2.3 (GND), X2.4 (GND)
unnamed: BAT1.+, U4.3 (VBAT)
unnamed: C6.1, U1.3
unnamed: C8.2, U1.11
unnamed: D2.+, J2.3 (LED), J2.4 (LED)
unnamed: J1.1 (ON), R3.2
unnamed: J2.1 (POWER), R6.1
unnamed: J2.2 (D13), R5.1
unnamed: N4.4 (TXD), R1.3, U1.4
unnamed: N4.5 (RXD), R2.1, R8.2
unnamed: N4.6 (~RTS), R1.2, U1.2
unnamed: N5.4 (TXD), U1.10
unnamed: N6.1 (VIN), Q1.S
unnamed: N10.19 (GPIO13_I2C2_SCL), R10.1, U4.6 (SCL)
unnamed: N10.20 (GPIO12_I2C2_SDA), R9.1, U4.5 (SDA)
unnamed: N5.5 (RXD), N8.2 (TXD), N10.21 (GPIO3_UART2_TX), R1.5, R8.5, U1.5
unnamed: N8.3 (RXD), N10.22 (GPIO2_UART2_RX), R7.1, R8.3
unnamed: N8.4 (~RESET), N10.31 (GPIO110_SPI1_SCLK), R1.4, R8.4, U1.12
unnamed: R7.2, U1.8
unnamed: U2.8 (STBY), U3.20 (PD6/OC2B)
unnamed: U4.1 (X1), X2.1
unnamed: U4.2 (X2), X2.2
VCC: C3.1, C4.1, C5.1, C7.1, D1.-, N6.3 (VOUT), N7.2 (5V), N9.4 (VTREF), N10.5 (VDD_5V), N10.6 (VDD_5V), R1.1, R4.2, R6.2, U1.1, U1.13, U1.14 (VCC), U2.3 (VDD), U2.5 (VIO), U3.10 (VCC), U3.30 (AVCC)

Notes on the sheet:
Console
Program
Note: U1 has ground connected to pin 7 and VCC connected to pin 14.
BUS HEADER
6-pin AVR ISP Connector
Jumper 1-3: Power LED Jumper 2-4: D13 LED Jumper 3-4: No LED
5V @ 1.5A DC/DC Converter
Filter Capacitors
Bus Transceiver
Reset Circuitry
AVR JTAG Connector
3V Lithium >100mAH
Real Time Clock

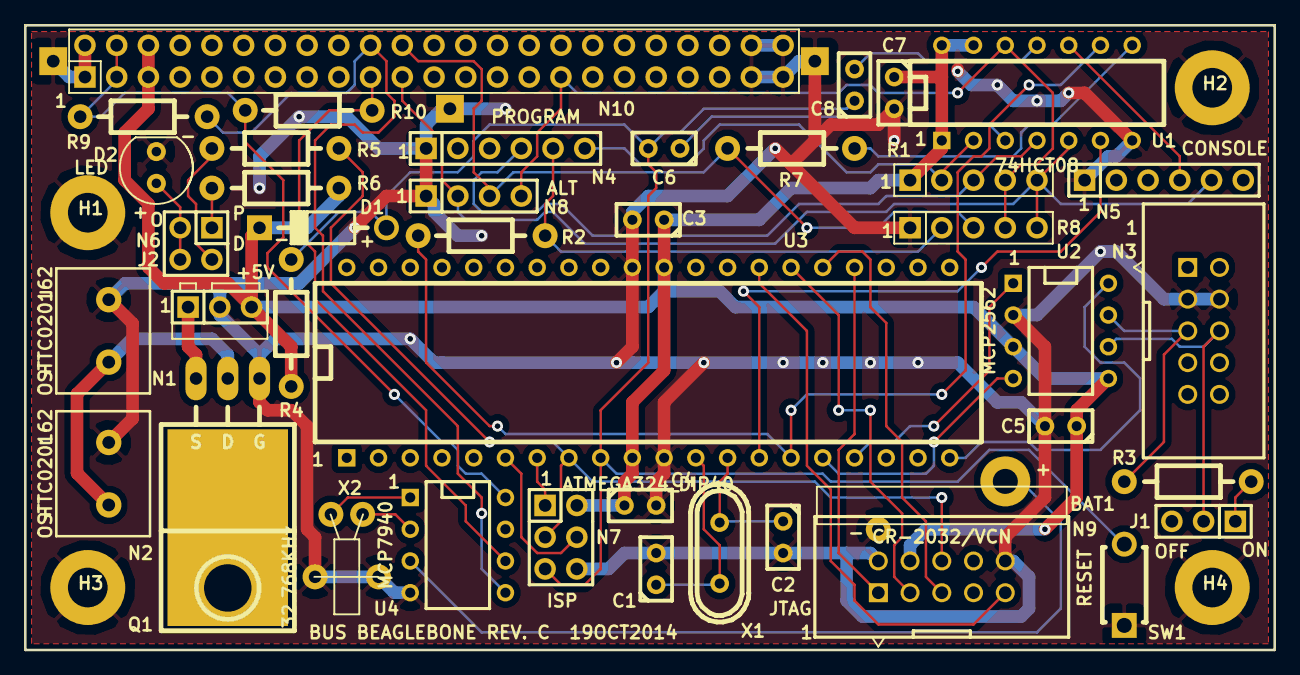
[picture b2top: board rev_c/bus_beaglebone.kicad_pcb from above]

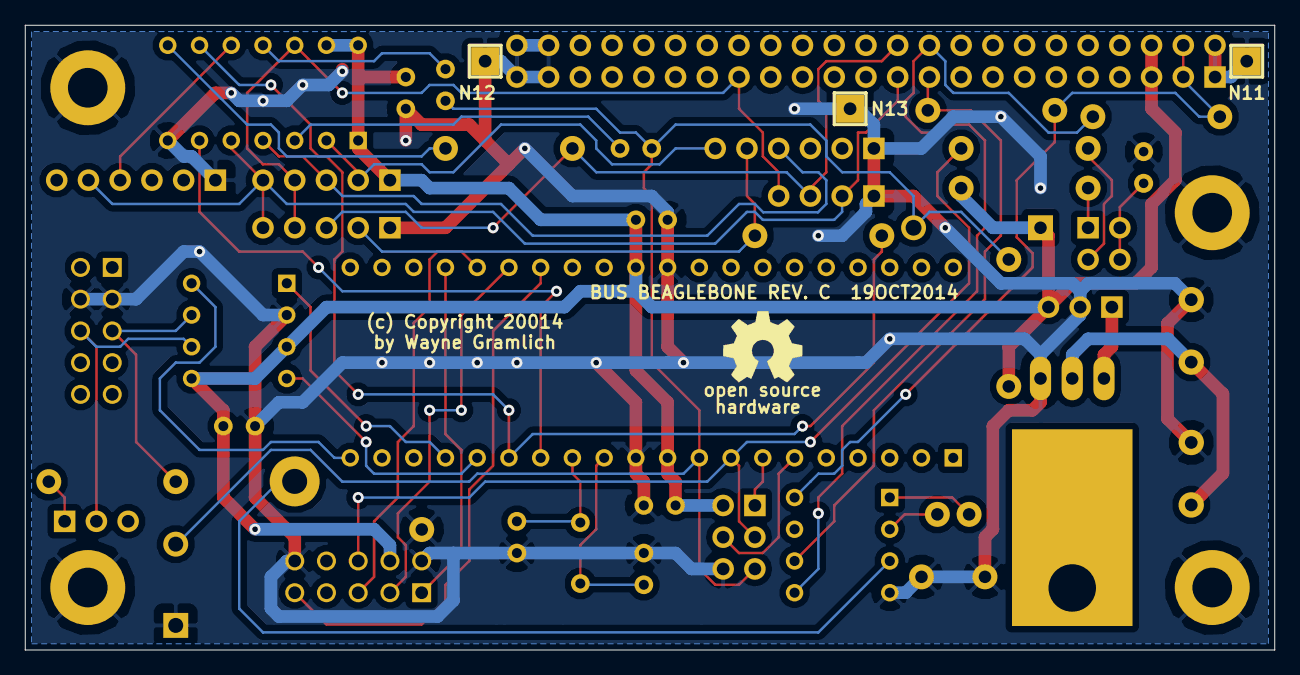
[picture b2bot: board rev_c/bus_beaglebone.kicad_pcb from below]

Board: 2 copper layers, 100.0 x 50.0 mm, 49 parts (4 on the bottom side), 41 nets.

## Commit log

2014-08-11 Made a clone of bus_raspberry_pi.
2014-08-11 Finnished doing clone of bus_raspberry_pi.
2014-08-11 Change out connector for BBB.
2014-08-11 Updated again.
2014-08-18 Added silkscreen outtline.
2014-08-18 Changed 22K=>22Kx 33K=>33Kx.
2014-10-04 Added fp-lib-table and updated .cmp/.net to use the new library name. Did not merge new net into PCB.
2014-10-04 Cloned Rev. B from Rev. .net file hase not been read in to PCB.
2014-10-05 Got Rev. B in pretty good shape.
2014-10-18 Checked in Rev. B
2014-10-19 Accidently skipped Rev.B to Rev. C clone commit. So this is Rev. C with the schematic updated, some new footprints, and the PCB modfications started.
2014-10-19 Wrapped up Rev. C.
2014-10-30 Wrapped up Rev. C
2014-11-09 Kludged bus_beaglebone.ino build in.
2014-12-10 Sending data over bus.
2014-12-10 Got two way bus communication going.
2014-12-12 Mostly code rearrangement.
2014-12-13 Got basic bus protocol working.
2014-12-16 Reorganized loop() routine.
2014-12-16 Bool8=>Logical Frame=>UShort.
2014-12-16 Switched over to using bus.frame_get() and bus.frame_put().
2014-12-16 Started removing Bus_Serial__* routines.
2014-12-17 Did first refactoring of master side code.
2014-12-17 More refactoring.
2014-12-17 Reformatted code to use Arduino standard of 2 space tabs.
2014-12-18 Got configurator talking over bus again.
2014-12-20 Talking to bus using AVR_UART1
2014-12-21 Got primitive UART0 kludged together.
2014-12-21 Missed reinitialized UCSR0B to enable TXEN0 and RXEN0.
2014-12-21 More UART clean-up.
2014-12-21 Got ECHO_TEST working again.
2014-12-22 Minor changes to Bus.h
2014-12-22 Got interrupts to start working.
2014-12-22 Got echo test working with full interrupts.
2014-12-23 Got command test working with interrupts.
2014-12-23 Got bridge working with interrupts.
2014-12-23 Got led set/get working over bus on actual bus_bridge_encoders_sonar board.
2015-01-01 Got bus protocol working better.
2015-01-01 Got PID stuff working.
2015-01-13 Rev. D is ready for manufacture.
2015-01-15 Converted 74HCT08 => 74HC08.
2015-03-05 Switched back to line mode.
2015-03-06 Got everything to compile inside a catkin workspace.
2015-03-06 Refactored sharable code over to bus_server.

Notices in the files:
rev_c/bus_beaglebone.kicad_pcb:
(c) Copyright 20014
rev_d/bus_beaglebone.kicad_pcb:
(C) 2015 GRAMLICH
